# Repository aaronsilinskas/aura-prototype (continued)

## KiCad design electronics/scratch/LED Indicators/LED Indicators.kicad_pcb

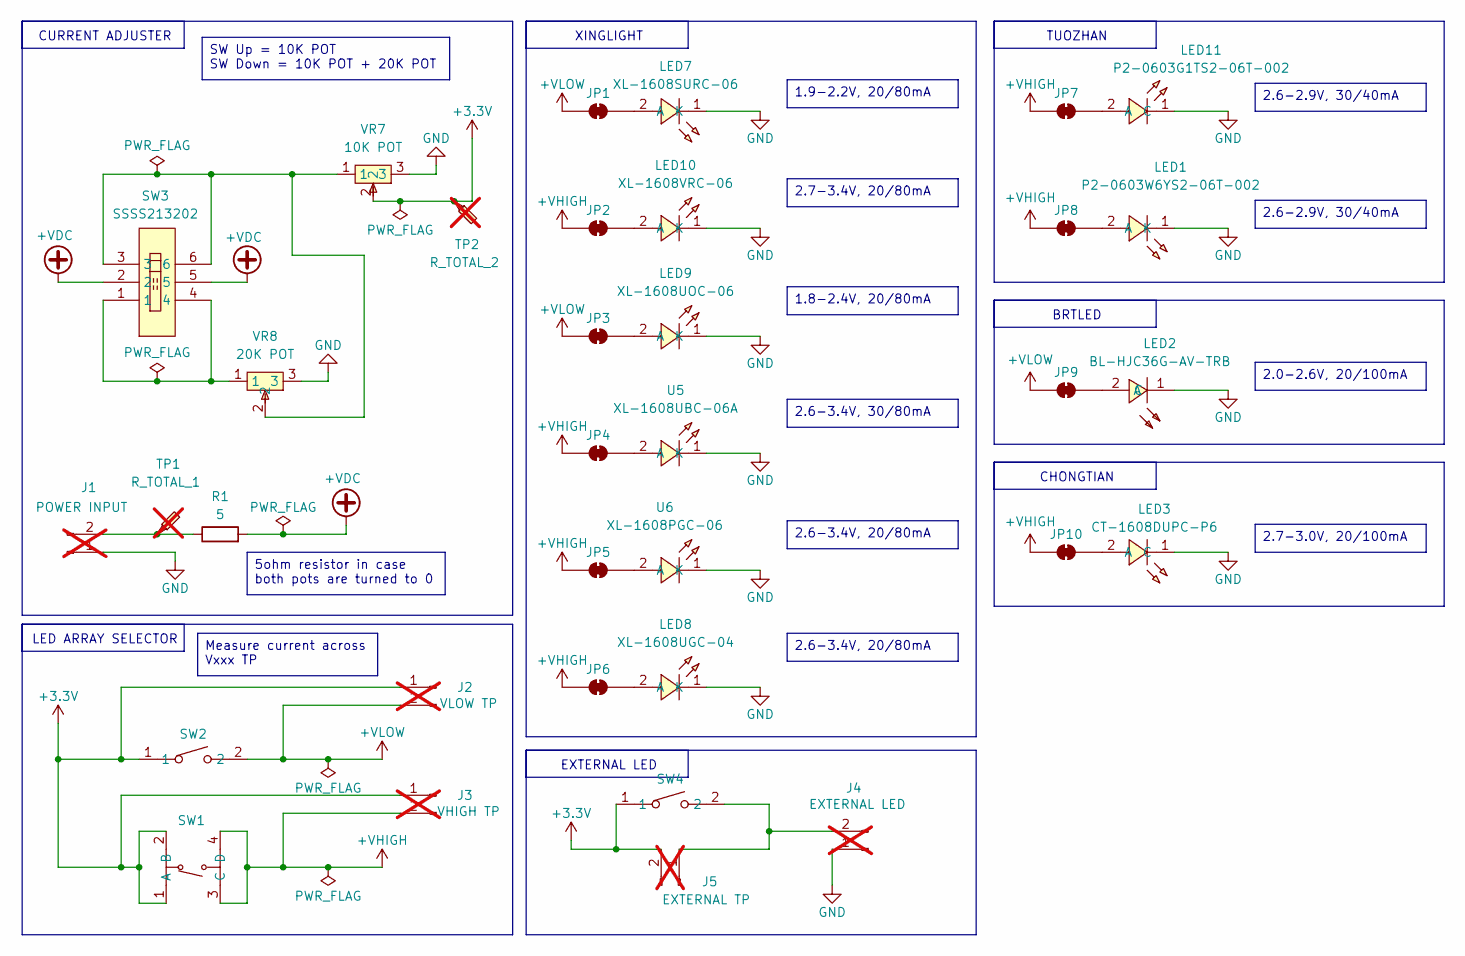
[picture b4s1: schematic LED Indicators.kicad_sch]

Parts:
J1: POWER INPUT; PinHeader_1x02_P2.54mm_Vertical; not fitted
J2: VLOW TP; PinHeader_1x02_P2.54mm_Vertical; not fitted
J3: VHIGH TP; PinHeader_1x02_P2.54mm_Vertical; not fitted
J4: EXTERNAL LED; PinHeader_1x02_P2.54mm_Vertical; not fitted
J5: EXTERNAL TP; PinHeader_1x02_P2.54mm_Vertical; not fitted
JP1, JP2, JP3, JP4, JP5, JP6, JP7, JP8, JP9, JP10: SolderJumper_2_Bridged; SolderJumper-2_P1.3mm_Bridged_RoundedPad1.0x1.5mm
LED1: P2-0603W6YS2-06T-002; LED-SMD_L1.6-W0.8-RD-WHITE-2; MPN F.0603.00048/P2-0603W6YS2-06T-002; LCSC Part C7496823
LED2: BL-HJC36G-AV-TRB; LED0603-R-RD_AMBER; MPN BL-HJC36G-AV-TRB; LCSC Part C165983
LED3: CT-1608DUPC-P6; LED-SMD_L1.6-W0.8-RD_CT-1608UWC-P4; MPN CT-1608DUPC-P6; LCSC Part C52676000
LED7: XL-1608SURC-06; LED0603-RD_RED; MPN XL-1608SURC-06; LCSC Part C965799
LED8: XL-1608UGC-04; LED0603-RD_GREEN; MPN XL-1608UGC-04; LCSC Part C965804
LED9: XL-1608UOC-06; LED0603-R-RD_ORANGE; MPN XL-1608UOC-06; LCSC Part C965800
LED10: XL-1608VRC-06; LED0603-RD_PINK; MPN XL-1608VRC-06; LCSC Part C7371906
LED11: P2-0603G1TS2-06T-002; LED0603-RD_GREEN; MPN F.0603.00025/P2-0603G1TS2-06T-002; LCSC Part C7496818
R1: 5; R_0805_2012Metric; LCSC Part C17724
SW1: TS-1187A-B-A-B; SW-SMD_4P-L5.1-W5.1-P3.70-LS6.5-TL_H1.5; MPN TS-1187A-B-A-B; LCSC Part C318884
SW2, SW4: TS-1088-AR02016; SW-SMD_L3.9-W3.0-P4.45; MPN TS-1088-AR02016; LCSC Part C720477
SW3: SSSS213202; SW-TH_SSSS213202; MPN SSSS213202; LCSC Part C115375
TP1: R_TOTAL_1; TestPoint_Pad_3.0x3.0mm; not fitted
TP2: R_TOTAL_2; TestPoint_Pad_3.0x3.0mm; not fitted
U5: XL-1608UBC-06A; LED0603-R-RD; MPN XL-1608UBC-06A; LCSC Part C7371904
U6: XL-1608PGC-06; LED0603-RD_GREEN; MPN XL-1608PGC-06; LCSC Part C7371905
VR7: 10K POT; RES-ADJ-SMD_3314J; MPN 3314J-1-103E; LCSC Part C36376
VR8: 20K POT; RES-ADJ-SMD_3P-L4.5-W4.5-P2.30-BL-FS; MPN 3314J-1-203E; LCSC Part C55069

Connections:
+3.3V: J2.1, J3.1, J5.2, SW1.1 (A), SW1.2 (B), SW2.1, SW4.1, TP2.1 (1_1), VR7.2
+VDC: R1.2, SW3.2, SW3.5
+VHIGH: J3.2, JP2.1 (A), JP4.1 (A), JP5.1 (A), JP6.1 (A), JP7.1 (A), JP8.1 (A), JP10.1 (A), SW1.3 (C), SW1.4 (D)
+VLOW: J2.2, JP1.1 (A), JP3.1 (A), JP9.1 (A), SW2.2
GND: J1.1, J4.1, LED1.1 (K), LED2.1 (C), LED3.1 (C), LED7.1 (K), LED8.1 (K), LED9.1 (K), LED10.1 (K), LED11.1 (C), U5.1 (K), U6.1 (K), VR7.3, VR8.3
unnamed: J1.2, R1.1, TP1.1 (1_1)
unnamed: J4.2, J5.1, SW4.2
unnamed: JP1.2 (B), LED7.2 (A)
unnamed: JP2.2 (B), LED10.2 (A)
unnamed: JP3.2 (B), LED9.2 (A)
unnamed: JP4.2 (B), U5.2 (A)
unnamed: JP5.2 (B), U6.2 (A)
unnamed: JP6.2 (B), LED8.2 (A)
unnamed: JP7.2 (B), LED11.2 (A)
unnamed: JP8.2 (B), LED1.2 (A)
unnamed: JP9.2 (B), LED2.2 (A)
unnamed: JP10.2 (B), LED3.2 (A)
unnamed: SW3.1, SW3.4, VR8.1
unnamed: SW3.3, SW3.6, VR7.1, VR8.2

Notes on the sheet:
BRTLED
XINGLIGHT
EXTERNAL LED
LED ARRAY SELECTOR
TUOZHAN
CURRENT ADJUSTER
CHONGTIAN
2.6-3.4V, 20/80mA
2.6-2.9V, 30/40mA
2.7-3.0V, 20/100mA
SW Up = 10K POT SW Down = 10K POT + 20K POT
2.6-3.4V, 30/80mA
1.8-2.4V, 20/80mA
2.0-2.6V, 20/100mA
1.9-2.2V, 20/80mA
2.7-3.4V, 20/80mA
Measure current across Vxxx TP
5ohm resistor in case both pots are turned to 0

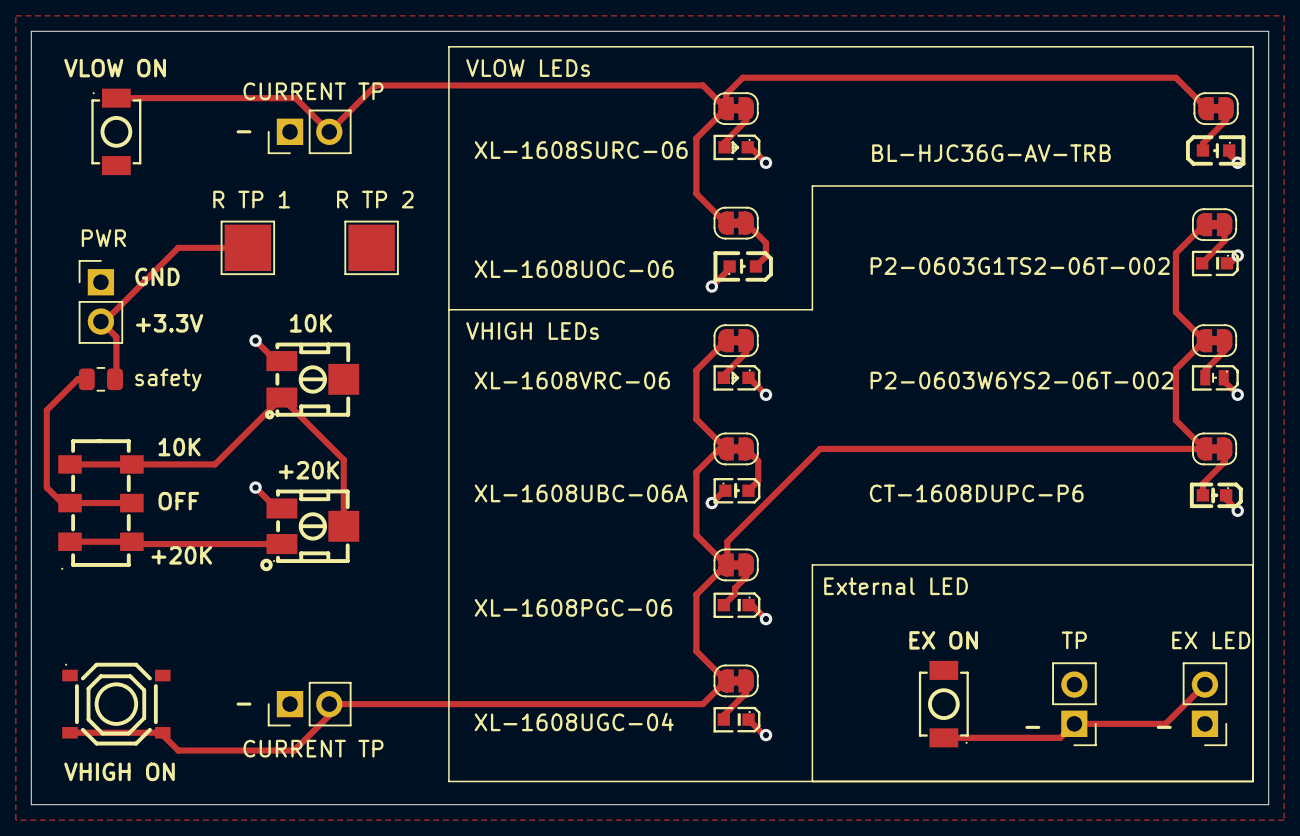
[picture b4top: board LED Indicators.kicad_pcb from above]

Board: 2 copper layers, 80.0 x 50.0 mm, 34 parts (0 on the bottom side), 19 nets.
